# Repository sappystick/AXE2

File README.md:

# AXE2

AXE2 is a clean-sheet 1-inch (D233 × 25.4 mm) pulse-induction detector head. Every part is produced by a generator: the housing parts, the routed boards (KiCad + Gerbers), the system netlist, the checks and the physics studies. The whole set is driven by one smart runner. Split from [ARX](https://github.com/sappystick/ARX) on 2026-10-30.

**Status:** MODELED / tool-checked. See `STATUS.md` (generated) and `START_HERE.md`.

```bash
make tools            # install + self-test (KiCad 9, libraries, ngspice, gmsh, ARM gcc, Java 25 + Freerouting, pinned Python)
python3 run.py        # run only what is needed: failed / changed / missing / dependents
python3 run.py --failed
```

| Folder | Contents |
|---|---|
| `rf2/head/` | head generators: SPEC + housing (`rf2_head.py`), system netlist, boards (`rf2_boards.py`, display `rf2_ledgrid.py`, shield, receive-board variant), checks, renders; outputs in `rf2/head/out/` |
| `rf2/` | physics studies (coil formation, receivers, ground, EMI, timing, pinpoint, ...), results, handoff, parts, enhancement plan |
| `src/pcb/` | routing and board tools: Freerouting step (stall watchdog), A* fallback router, Gerber geometry, DRC helpers, SB1R generator |
| `reference/rf1/` | RF1 rigid-flex work: routed AB1A / AB1B, CB1D placement (Phase C starts here) |
| `data/` | datasheets (verified values in `docs/DATASHEET_LOG_ARX.md`), reference inputs |
| `state/` | runner ledger (results of every step); logs are not committed |
| `docs/` | references to ARX, corrections, assumptions, conventions |

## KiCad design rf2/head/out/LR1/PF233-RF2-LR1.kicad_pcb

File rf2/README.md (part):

# RF2 clean-sheet side experiment: transmit formation in a 1-inch head (MODELED)

Question (owner, 2026-10-29): inside the existing diameter and a 1-inch (25.4 mm) height, which layered / stacked / dense transmit-coil formation gives
the most depth together with the best signature data, with the dual-quadrupole receiver (RX-Q) and a central rigid-flex compute bay?
Nothing here touches the baseline. All numbers are MODELED: noise-limited, gold spheres, no ground, no bench data.

`rf2_coil_search.py` (about 20 s) -> `results/rf2_coil_search.json`; `rf2_figure.py` -> `results/rf2_coil_search.png`.

## Method
- Same physics as `src/sim/sim_head1.py`, re-parametrised: RX-Q geometry and noise, sphere step-off response, gate schedule, SNR 3, lateral search grid,
  the turn-off circuit and the first clean gate from the nulled turn-off tail (floor 6 us).
- **Fair comparison:** every candidate gets the baseline's energy per pulse at boost (1/2 x 54 uH x 20 A^2 = 10.8 mJ) and 20 A per switch. With the energy
  fixed, depth depends on the winding geometry through B / sqrt(L) only; the series / parallel split just trades current for inductance, and more switches
  (more total current at the same energy) make the turn-off faster.
- Coil: circular turns (exact elliptic-integral fields and inductances), litz 1.2 mm OD on a dense 1.6 mm grid, window z 3.2-21.9 mm (RX-Q boards below,
  lid + ferrite sheet + clearance above; the display sits in the centre bay), r up to 113.4 mm.
- **Validation:** the built coil through this chain: L 51.5 uH (model 54), 25.0 uT/A at 100 mm (24.56), moment 7.97 A m2 at 20 A (7.96), depth
  0.1 / 1 / 20 g = 90 / 134 / 188 mm (sim_head1: 91 / 136 / 189).

## Results (1 g / 0.1 g gold sphere, RX-Q)
| Formation | 1 g | 0.1 g | Notes |
|---|---|---|---|
| Built coil (25.6 mm tall, does not fit 1 in) | 134 | 90 | first gate 7.1 us |
| 1 in, dense window r 62-113 (spread) ... r 100-113 (rim), 1 switch | 136 | 91-92 | geometry changes depth by <= 1 mm at fixed energy |
| 1 in, rim r 100-113, 2 or 4 switches | 137 | 94 | turn-off 3.8 -> 1.9 us; first gate reaches the 6 us receiver floor |
| + ideal ferrite plane above (UPPER BOUND) | 143 | 98 | the real hood v3 model gave about half of an ideal plane's gain |
| Quadrant set, X mode (horizontal field, shape probe) | 131 | 93 | nearly as deep as the vertical mode with RX-Q |
| Built coil with the figure-8 receiver (sim_head1) | 152 | 99 | the receiver, not the transmit formation, is the largest depth lever |

First-gate sensitivity (4-switch rim coil): 6 / 4 / 3 / 2 us -> 0.05 g 79 / 85 / 88 / 91 mm, 0.1 g 94 / 98 / 100 / 102 mm, 1 g 137 / 139 / 139 / 140 mm.

## Reading
1. **A 1-inch head costs no depth.** At the same pulse energy the dense 1-inch windings match or beat the 25.6 mm stacked coil (136-137 vs 134 mm).
2. **No transmit formation is a big depth lever in this footprint.** Spreading or concentrating the turns, stacking or not: <= 2 mm. Depth moves with
   pulse energy (signal ~ sqrt(E): 2 x energy -> about +7 %), the receiver (figure-8 152 vs RX-Q 136 mm: RX-Q trades about 11 % depth for bearing and
   pinpoint), noise and averaging.
3. **Best formation for depth + signature:** a dense rim winding (r about 100-113 mm, full window height) split into interleaved full-ring branches on
   2-4 switches: fastest turn-off at the same energy (better small / fast targets once the receiver recovers sooner), same depth, frees the centre bay.
4. **Quadrant windings (Z + X / Y modes) give a strong shape channel (X mode 131 mm at 1 g) but a 1 % current mismatch between quadrants puts about
   0.49 V into RX-Q at turn-off** (the built coil's aligned leak is 0.01 mV). The vertical mode must stay on symmetric full-ring branches; X / Y needs
   its own matched pair winding and a receiver that recovers from that leak. Not yet modeled: the pairs' turn-off, X-mode energy, recovery.
5. **Small targets:** the remaining limit is the receiver recovery floor, not the coil: 6 -> 2 us adds about 15 % depth on 0.05 g.

## Not modeled
Ground (mineralisation: the early gates that help small gold also see more ground), coil self-capacitance, litz AC resistance, eddy currents in the head
and the compute bay, the real (finite) ferrite sheet, thermal. Next if pursued: figure-8 / DD / concentric receive options in the same chain with the
rim coil, a matched X / Y pair winding with its turn-off and leak, a finite ferrite sheet, and ground.

## Step 2: receiver architecture, light coil, mass, and an SDC 2300-class comparison (`rf2_receiver_combo.py`, `results/rf2_receiver_combo.{json,png}`)
Owner: targets of 1 g and up only. Same physics and equal energy per pulse (10.8 mJ); every receive channel read with the same preamp noise (1.7 nV/rtHz).

| Architecture (1-inch head, rim transmit coil) | 1 g | 5 g | 20 g | Uniform-ground coupling (rel. CN) |
|---|---|---|---|---|
| QUAD only (built receiver) | 137 | 165 | 190 | 0 by symmetry |
| Figure-8 only (check: sim_head1 at the same noise gives 179 mm at 1 g) | 181 | 223 | 262 | 0 by symmetry |
| Concentric nulled (12 turns r 80-95, 26 bucking turns r 65) | 231 | 284 | 337 | 1.0 |
| **Proposed: rim mono (26 turns, 321 uH, 8.2 A) + QUAD board, mono channel, 15 us gate** | **345** | **439** | **>= 500** | 1.44 |
| same, QUAD channel (bearing, pinpoint, depth ratio) | 131 | 162 | 189 | 0 by symmetry |
| SDC 2300-class 8 in mono at EQUAL electronics, 10 us gate (internals ASSUMED) | 330 | 413 | 494 | 1.40 |

- **Light transmit winding:** 24 turns (16.9 m of litz) give the same depth as the 99-turn dense window (66.6 m): at fixed energy only B / sqrt(L) counts.
- **Depth readout:** the QUAD / mono peak-signal ratio falls monotonically with depth (0.118 / 0.026 / 0.0094 / 0.0043 / 0.0019 at 50 / 100 / 150 / 200 / 300 mm),
  independent of target size for a sphere: depth from the ratio, then size from the amplitude at that depth, type from the decay time constant.
- **Head mass estimate: about 0.53 kg** (component estimates, not weighed; baseline head estimate 2.22 kg). The SDC 2300 is 2.3-2.4 kg as a whole
  detector without batteries; its coil mass is not published, so no head-to-head mass comparison is made.
- **SDC 2300 published facts used:** 8 in round mono, hardwired; Multi Period Fast PI; 2.3-2.4 kg without batteries; 4 x C cells, about 7 h; no
  discrimination, depth readout or pinpoint mode; LED indicator + audio; waterproof 3 m. Not published: turns, inductance, current, timing, noise, depth.
  The SDC row is therefore an 8 in mono with OUR electronics, not the real detector.
- **Reading:** the mono channel is the deepest receive option for >= 1 g (the full transmit coil is the receiver: the largest area); the proposed
  head's mono is about 4-5 % deeper than an 8 in mono at equal electronics, from the larger diameter only. What the proposed head adds is the QUAD
  channel (bearing, peak-null-peak pinpoint, a ground-symmetric second channel) and the ratio depth readout.
- **The bucking-turn cap:** an unconstrained concentric search chose 1239 turns at r 12 mm (cannot be laid out; capacitance and resistance noise not
  modeled); the search caps the bucking winding at 30 board-trace turns (0.3 mm pitch, 4 layers, a 6 mm band holds about 80).
- **Not modeled, and decisive in the field:** real ground. The mono and CN channels see a uniform viscous ground strongly and need ground balance
  (as the SDC has); the QUAD and figure-8 cancel uniform ground only while the head stays level and at constant height. Hot rocks, layering and
  sweep tilt are not modeled. Also not modeled: the mono's damping-resistor noise and preamp overload recovery (the 1.7 nV/rtHz is generous to both
  monos), self-capacitance, eddy currents in the compute bay.

## Step 3: mineralised ground and how to cancel it (`rf2_ground.py`, `results/rf2_ground.{json,png}`)
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
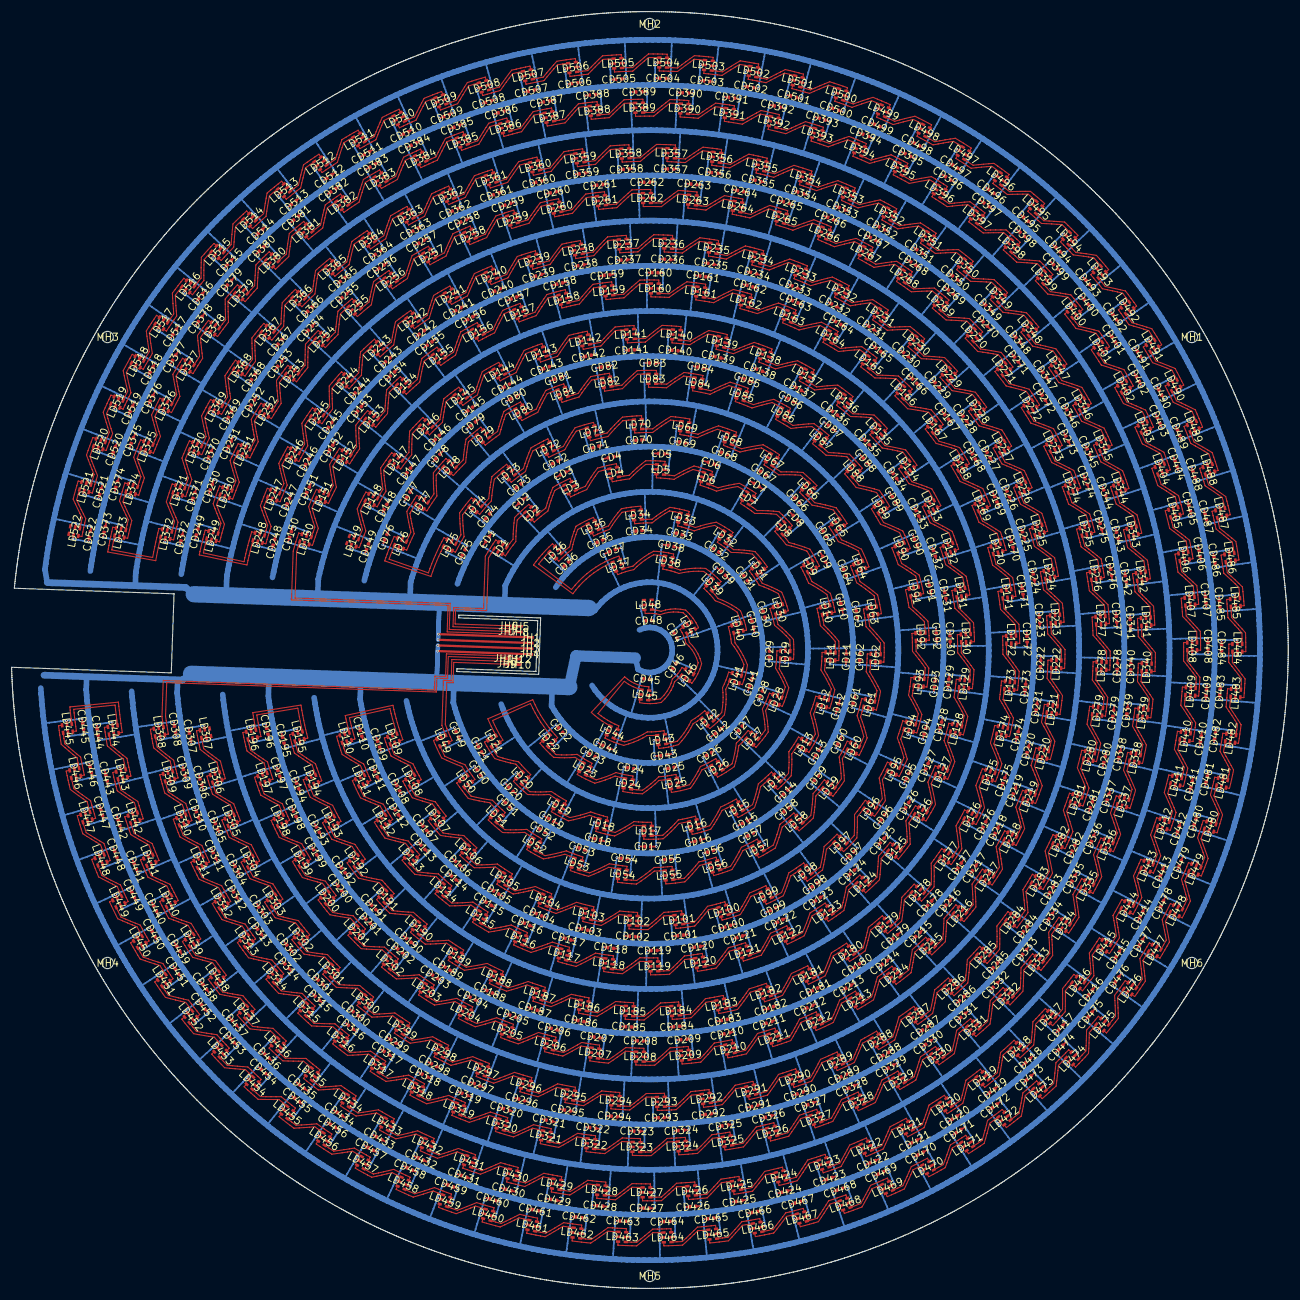
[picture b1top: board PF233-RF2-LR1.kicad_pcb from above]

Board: 2 copper layers, 226.0 x 226.0 mm, 1062 parts (0 on the bottom side), 1046 nets.

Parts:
CD1, CD2, CD3, CD4, CD5, CD6, CD7, CD8, CD9, CD10, CD11, CD12, CD13, CD14, CD15, CD16, CD17, CD18, CD19, CD20, CD21, CD22, CD23, CD24, CD25, CD26, CD27, CD28, CD29, CD30, CD31, CD32, CD33, CD34, CD35, CD36, CD37, CD38, CD39, CD40, CD41, CD42, CD43, CD44, CD45, CD46, CD47, CD48, CD49, CD50, CD51, CD52, CD53, CD54, CD55, CD56, CD57, CD58, CD59, CD60, CD61, CD62, CD63, CD64, CD65, CD66, CD67, CD68, CD69, CD70, CD71, CD72, CD73, CD74, CD75, CD76, CD77, CD78, CD79, CD80, CD81, CD82, CD83, CD84, CD85, CD86, CD87, CD88, CD89, CD90, CD91, CD92, CD93, CD94, CD95, CD96, CD97, CD98, CD99, CD100, CD101, CD102, CD103, CD104, CD105, CD106, CD107, CD108, CD109, CD110, CD111, CD112, CD113, CD114, CD115, CD116, CD117, CD118, CD119, CD120, CD121, CD122, CD123, CD124, CD125, CD126, CD127, CD128, CD129, CD130, CD131, CD132, CD133, CD134, CD135, CD136, CD137, CD138, CD139, CD140, CD141, CD142, CD143, CD144, CD145, CD146, CD147, CD148, CD149, CD150, CD151, CD152, CD153, CD154, CD155, CD156, CD157, CD158, CD159, CD160, CD161, CD162, CD163, CD164, CD165, CD166, CD167, CD168, CD169, CD170, CD171, CD172, CD173, CD174, CD175, CD176, CD177, CD178, CD179, CD180, CD181, CD182, CD183, CD184, CD185, CD186, CD187, CD188, CD189, CD190, CD191, CD192, CD193, CD194, CD195, CD196, CD197, CD198, CD199, CD200, CD201, CD202, CD203, CD204, CD205, CD206, CD207, CD208, CD209, CD210, CD211, CD212, CD213, CD214, CD215, CD216, CD217, CD218, CD219, CD220, CD221, CD222, CD223, CD224, CD225, CD226, CD227, CD228, CD229, CD230, CD231, CD232, CD233, CD234, CD235, CD236, CD237, CD238, CD239, CD240, CD241, CD242, CD243, CD244, CD245, CD246, CD247, CD248, CD249, CD250, CD251, CD252, CD253, CD254, CD255, CD256, CD257, CD258, CD259, CD260, CD261, CD262, CD263, CD264, CD265, CD266, CD267, CD268, CD269, CD270, CD271, CD272, CD273, CD274, CD275, CD276, CD277, CD278, CD279, CD280, CD281, CD282, CD283, CD284, CD285, CD286, CD287, CD288, CD289, CD290, CD291, CD292, CD293, CD294, CD295, CD296, CD297, CD298, CD299, CD300, CD301, CD302, CD303, CD304, CD305, CD306, CD307, CD308, CD309, CD310, CD311, CD312, CD313, CD314, CD315, CD316, CD317, CD318, CD319, CD320, CD321, CD322, CD323, CD324, CD325, CD326, CD327, CD328, CD329, CD330, CD331, CD332, CD333, CD334, CD335, CD336, CD337, CD338, CD339, CD340, CD341, CD342, CD343, CD344, CD345, CD346, CD347, CD348, CD349, CD350, CD351, CD352, CD353, CD354, CD355, CD356, CD357, CD358, CD359, CD360, CD361, CD362, CD363, CD364, CD365, CD366, CD367, CD368, CD369, CD370, CD371, CD372, CD373, CD374, CD375, CD376, CD377, CD378, CD379, CD380, CD381, CD382, CD383, CD384, CD385, CD386, CD387, CD388, CD389, CD390, CD391, CD392, CD393, CD394, CD395, CD396, CD397, CD398, CD399, CD400, CD401, CD402, CD403, CD404, CD405, CD406, CD407, CD408, CD409, CD410, CD411, CD412, CD413, CD414, CD415, CD416, CD417, CD418, CD419, CD420, CD421, CD422, CD423, CD424, CD425, CD426, CD427, CD428, CD429, CD430, CD431, CD432, CD433, CD434, CD435, CD436, CD437, CD438, CD439, CD440, CD441, CD442, CD443, CD444, CD445, CD446, CD447, CD448, CD449, CD450, CD451, CD452, CD453, CD454, CD455, CD456, CD457, CD458, CD459, CD460, CD461, CD462, CD463, CD464, CD465, CD466, CD467, CD468, CD469, CD470, CD471, CD472, CD473, CD474, CD475, CD476, CD477, CD478, CD479, CD480, CD481, CD482, CD483, CD484, CD485, CD486, CD487, CD488, CD489, CD490, CD491, CD492, CD493, CD494, CD495, CD496, CD497, CD498, CD499, CD500, CD501, CD502, CD503, CD504, CD505, CD506, CD507, CD508, CD509, CD510, CD511, CD512, CD513, CD514, CD515, CD516, CD517, CD518, CD519, CD520, CD521, CD522: 100n; C0402
JH1, JH2: GND; FLEX_LAND
JH3, JH4: +5V_LED; FLEX_LAND
JH5: C1_K0; FLEX_LAND
JH6: C1_D0; FLEX_LAND
JH7: C3_D0; FLEX_LAND
JH8: C3_K0; FLEX_LAND
JH9: C2_K0; FLEX_LAND
JH10: C2_D0; FLEX_LAND
JH11: C4_K0; FLEX_LAND
JH12: C4_D0; FLEX_LAND
LD1, LD2, LD3, LD4, LD5, LD6, LD7, LD8, LD9, LD10, LD11, LD12, LD13, LD14, LD15, LD16, LD17, LD18, LD19, LD20, LD21, LD22, LD23, LD24, LD25, LD26, LD27, LD28, LD29, LD30, LD31, LD32, LD33, LD34, LD35, LD36, LD37, LD38, LD39, LD40, LD41, LD42, LD43, LD44, LD45, LD46, LD47, LD48, LD49, LD50, LD51, LD52, LD53, LD54, LD55, LD56, LD57, LD58, LD59, LD60, LD61, LD62, LD63, LD64, LD65, LD66, LD67, LD68, LD69, LD70, LD71, LD72, LD73, LD74, LD75, LD76, LD77, LD78, LD79, LD80, LD81, LD82, LD83, LD84, LD85, LD86, LD87, LD88, LD89, LD90, LD91, LD92, LD93, LD94, LD95, LD96, LD97, LD98, LD99, LD100, LD101, LD102, LD103, LD104, LD105, LD106, LD107, LD108, LD109, LD110, LD111, LD112, LD113, LD114, LD115, LD116, LD117, LD118, LD119, LD120, LD121, LD122, LD123, LD124, LD125, LD126, LD127, LD128, LD129, LD130, LD131, LD132, LD133, LD134, LD135, LD136, LD137, LD138, LD139, LD140, LD141, LD142, LD143, LD144, LD145, LD146, LD147, LD148, LD149, LD150, LD151, LD152, LD153, LD154, LD155, LD156, LD157, LD158, LD159, LD160, LD161, LD162, LD163, LD164, LD165, LD166, LD167, LD168, LD169, LD170, LD171, LD172, LD173, LD174, LD175, LD176, LD177, LD178, LD179, LD180, LD181, LD182, LD183, LD184, LD185, LD186, LD187, LD188, LD189, LD190, LD191, LD192, LD193, LD194, LD195, LD196, LD197, LD198, LD199, LD200, LD201, LD202, LD203, LD204, LD205, LD206, LD207, LD208, LD209, LD210, LD211, LD212, LD213, LD214, LD215, LD216, LD217, LD218, LD219, LD220, LD221, LD222, LD223, LD224, LD225, LD226, LD227, LD228, LD229, LD230, LD231, LD232, LD233, LD234, LD235, LD236, LD237, LD238, LD239, LD240, LD241, LD242, LD243, LD244, LD245, LD246, LD247, LD248, LD249, LD250, LD251, LD252, LD253, LD254, LD255, LD256, LD257, LD258, LD259, LD260, LD261, LD262, LD263, LD264, LD265, LD266, LD267, LD268, LD269, LD270, LD271, LD272, LD273, LD274, LD275, LD276, LD277, LD278, LD279, LD280, LD281, LD282, LD283, LD284, LD285, LD286, LD287, LD288, LD289, LD290, LD291, LD292, LD293, LD294, LD295, LD296, LD297, LD298, LD299, LD300, LD301, LD302, LD303, LD304, LD305, LD306, LD307, LD308, LD309, LD310, LD311, LD312, LD313, LD314, LD315, LD316, LD317, LD318, LD319, LD320, LD321, LD322, LD323, LD324, LD325, LD326, LD327, LD328, LD329, LD330, LD331, LD332, LD333, LD334, LD335, LD336, LD337, LD338, LD339, LD340, LD341, LD342, LD343, LD344, LD345, LD346, LD347, LD348, LD349, LD350, LD351, LD352, LD353, LD354, LD355, LD356, LD357, LD358, LD359, LD360, LD361, LD362, LD363, LD364, LD365, LD366, LD367, LD368, LD369, LD370, LD371, LD372, LD373, LD374, LD375, LD376, LD377, LD378, LD379, LD380, LD381, LD382, LD383, LD384, LD385, LD386, LD387, LD388, LD389, LD390, LD391, LD392, LD393, LD394, LD395, LD396, LD397, LD398, LD399, LD400, LD401, LD402, LD403, LD404, LD405, LD406, LD407, LD408, LD409, LD410, LD411, LD412, LD413, LD414, LD415, LD416, LD417, LD418, LD419, LD420, LD421, LD422, LD423, LD424, LD425, LD426, LD427, LD428, LD429, LD430, LD431, LD432, LD433, LD434, LD435, LD436, LD437, LD438, LD439, LD440, LD441, LD442, LD443, LD444, LD445, LD446, LD447, LD448, LD449, LD450, LD451, LD452, LD453, LD454, LD455, LD456, LD457, LD458, LD459, LD460, LD461, LD462, LD463, LD464, LD465, LD466, LD467, LD468, LD469, LD470, LD471, LD472, LD473, LD474, LD475, LD476, LD477, LD478, LD479, LD480, LD481, LD482, LD483, LD484, LD485, LD486, LD487, LD488, LD489, LD490, LD491, LD492, LD493, LD494, LD495, LD496, LD497, LD498, LD499, LD500, LD501, LD502, LD503, LD504, LD505, LD506, LD507, LD508, LD509, LD510, LD511, LD512, LD513, LD514, LD515, LD516, LD517, LD518, LD519, LD520, LD521, LD522: SK9822-EC20; SK9822EC20
MH1, MH2, MH3, MH4, MH5, MH6: MountingHole_2.0mm

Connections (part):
+5V_LED: CD1.1, CD2.1, CD3.1, CD4.1, CD5.1, CD6.1, CD7.1, CD8.1, CD9.1, CD10.1, CD11.1, CD12.1, CD13.1, CD14.1, CD15.1, CD16.1, CD17.1, CD18.1, CD19.1, CD20.1, CD21.1, CD22.1, CD23.1, CD24.1, CD25.1, CD26.1, CD27.1, CD28.1, CD29.1, CD30.1, CD31.1, CD32.1, CD33.1, CD34.1, CD35.1, CD36.1, CD37.1, CD38.1, CD39.1, CD40.1, CD41.1, CD42.1, CD43.1, CD44.1, CD45.1, CD46.1, CD47.1, CD48.1, CD49.1, CD50.1, CD51.1, CD52.1, CD53.1, CD54.1, CD55.1, CD56.1, CD57.1, CD58.1, CD59.1, CD60.1, CD61.1, CD62.1, CD63.1, CD64.1, CD65.1, CD66.1, CD67.1, CD68.1, CD69.1, CD70.1, CD71.1, CD72.1, CD73.1, CD74.1, CD75.1, CD76.1, CD77.1, CD78.1, CD79.1, CD80.1, CD81.1, CD82.1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
C1_D0: JH6.1, LD1.3
C1_D1: LD1.1, LD2.3
C1_D2: LD2.1, LD3.3
C1_D3: LD3.1, LD4.3
C1_D4: LD4.1, LD5.3
C1_D5: LD5.1, LD6.3
C1_D6: LD6.1, LD7.3
C1_D7: LD7.1, LD8.3
C1_D8: LD8.1, LD9.3
C1_D9: LD9.1, LD10.3
C1_D10: LD10.1, LD11.3
C1_D11: LD11.1, LD12.3
C1_D12: LD12.1, LD13.3
C1_D13: LD13.1, LD14.3
C1_D14: LD14.1, LD15.3
C1_D15: LD15.1, LD16.3
C1_D16: LD16.1, LD17.3
C1_D17: LD17.1, LD18.3
C1_D18: LD18.1, LD19.3
C1_D19: LD19.1, LD20.3
C1_D20: LD20.1, LD21.3
C1_D21: LD21.1, LD22.3
C1_D22: LD22.1, LD23.3
C1_D23: LD23.1, LD24.3
C1_D24: LD24.1, LD25.3
C1_D25: LD25.1, LD26.3
C1_D26: LD26.1, LD27.3
C1_D27: LD27.1, LD28.3
C1_D28: LD28.1, LD29.3
C1_D29: LD29.1, LD30.3
C1_D30: LD30.1, LD31.3
C1_D31: LD31.1, LD32.3
C1_D32: LD32.1, LD33.3
C1_D33: LD33.1, LD34.3
C1_D34: LD34.1, LD35.3
C1_D35: LD35.1, LD36.3
C1_D36: LD36.1, LD37.3
C1_D37: LD37.1, LD38.3
C1_D38: LD38.1, LD39.3
C1_D39: LD39.1, LD40.3
C1_D40: LD40.1, LD41.3
C1_D41: LD41.1, LD42.3
C1_D42: LD42.1, LD43.3
C1_D43: LD43.1, LD44.3
C1_D44: LD44.1, LD45.3
C1_D45: LD45.1, LD46.3
C1_D46: LD46.1, LD47.3
C1_D47: LD47.1, LD48.3
C1_K0: JH5.1, LD1.4
C1_K1: LD1.6, LD2.4
C1_K2: LD2.6, LD3.4
C1_K3: LD3.6, LD4.4
C1_K4: LD4.6, LD5.4
C1_K5: LD5.6, LD6.4
C1_K6: LD6.6, LD7.4
C1_K7: LD7.6, LD8.4
C1_K8: LD8.6, LD9.4
C1_K9: LD9.6, LD10.4
C1_K10: LD10.6, LD11.4
C1_K11: LD11.6, LD12.4
C1_K12: LD12.6, LD13.4
C1_K13: LD13.6, LD14.4
C1_K14: LD14.6, LD15.4
C1_K15: LD15.6, LD16.4
C1_K16: LD16.6, LD17.4
C1_K17: LD17.6, LD18.4
C1_K18: LD18.6, LD19.4
C1_K19: LD19.6, LD20.4
C1_K20: LD20.6, LD21.4
C1_K21: LD21.6, LD22.4
C1_K22: LD22.6, LD23.4
C1_K23: LD23.6, LD24.4
C1_K24: LD24.6, LD25.4
C1_K25: LD25.6, LD26.4
C1_K26: LD26.6, LD27.4
C1_K27: LD27.6, LD28.4
C1_K28: LD28.6, LD29.4
C1_K29: LD29.6, LD30.4
C1_K30: LD30.6, LD31.4
C1_K31: LD31.6, LD32.4
C1_K32: LD32.6, LD33.4
C1_K33: LD33.6, LD34.4
C1_K34: LD34.6, LD35.4
C1_K35: LD35.6, LD36.4
C1_K36: LD36.6, LD37.4
C1_K37: LD37.6, LD38.4
C1_K38: LD38.6, LD39.4
C1_K39: LD39.6, LD40.4
C1_K40: LD40.6, LD41.4
C1_K41: LD41.6, LD42.4
C1_K42: LD42.6, LD43.4
C1_K43: LD43.6, LD44.4
C1_K44: LD44.6, LD45.4
C1_K45: LD45.6, LD46.4
C1_K46: LD46.6, LD47.4
C1_K47: LD47.6, LD48.4
C2_D0: JH10.1, LD49.3
C2_D1: LD49.1, LD50.3
C2_D2: LD50.1, LD51.3
C2_D3: LD51.1, LD52.3
C2_D4: LD52.1, LD53.3
C2_D5: LD53.1, LD54.3
C2_D6: LD54.1, LD55.3
C2_D7: LD55.1, LD56.3
C2_D8: LD56.1, LD57.3
C2_D9: LD57.1, LD58.3
C2_D10: LD58.1, LD59.3
C2_D11: LD59.1, LD60.3
C2_D12: LD60.1, LD61.3
C2_D13: LD61.1, LD62.3
C2_D14: LD62.1, LD63.3
C2_D15: LD63.1, LD64.3
C2_D16: LD64.1, LD65.3
C2_D17: LD65.1, LD66.3
C2_D18: LD66.1, LD67.3
C2_D19: LD67.1, LD68.3
C2_D20: LD68.1, LD69.3
C2_D21: LD69.1, LD70.3
C2_D22: LD70.1, LD71.3
C2_D23: LD71.1, LD72.3
C2_D24: LD72.1, LD73.3
C2_D25: LD73.1, LD74.3
C2_D26: LD74.1, LD75.3
C2_D27: LD75.1, LD76.3
C2_D28: LD76.1, LD77.3
C2_D29: LD77.1, LD78.3
C2_D30: LD78.1, LD79.3
C2_D31: LD79.1, LD80.3
C2_D32: LD80.1, LD81.3
C2_D33: LD81.1, LD82.3
C2_D34: LD82.1, LD83.3
C2_D35: LD83.1, LD84.3
C2_D36: LD84.1, LD85.3
C2_D37: LD85.1, LD86.3
C2_D38: LD86.1, LD87.3
C2_D39: LD87.1, LD88.3
C2_D40: LD88.1, LD89.3
C2_D41: LD89.1, LD90.3
C2_D42: LD90.1, LD91.3
C2_D43: LD91.1, LD92.3
C2_D44: LD92.1, LD93.3
C2_D45: LD93.1, LD94.3
C2_D46: LD94.1, LD95.3
C2_D47: LD95.1, LD96.3
C2_D48: LD96.1, LD97.3
C2_D49: LD97.1, LD98.3
C2_D50: LD98.1, LD99.3
C2_D51: LD99.1, LD100.3
C2_D52: LD100.1, LD101.3
C2_D53: LD101.1, LD102.3
C2_D54: LD102.1, LD103.3
C2_D55: LD103.1, LD104.3
C2_D56: LD104.1, LD105.3
C2_D57: LD105.1, LD106.3
C2_D58: LD106.1, LD107.3
C2_D59: LD107.1, LD108.3
C2_D60: LD108.1, LD109.3
C2_D61: LD109.1, LD110.3
C2_D62: LD110.1, LD111.3
C2_D63: LD111.1, LD112.3
C2_D64: LD112.1, LD113.3
C2_D65: LD113.1, LD114.3
C2_D66: LD114.1, LD115.3
C2_D67: LD115.1, LD116.3
C2_D68: LD116.1, LD117.3
C2_D69: LD117.1, LD118.3
C2_D70: LD118.1, LD119.3
C2_D71: LD119.1, LD120.3
C2_D72: LD120.1, LD121.3
C2_D73: LD121.1, LD122.3
C2_D74: LD122.1, LD123.3
C2_D75: LD123.1, LD124.3
C2_D76: LD124.1, LD125.3
C2_D77: LD125.1, LD126.3
C2_D78: LD126.1, LD127.3
C2_D79: LD127.1, LD128.3
C2_D80: LD128.1, LD129.3
C2_D81: LD129.1, LD130.3
C2_D82: LD130.1, LD131.3
C2_D83: LD131.1, LD132.3
C2_D84: LD132.1, LD133.3
C2_D85: LD133.1, LD134.3
C2_D86: LD134.1, LD135.3
C2_D87: LD135.1, LD136.3
C2_D88: LD136.1, LD137.3
C2_D89: LD137.1, LD138.3
C2_D90: LD138.1, LD139.3
C2_D91: LD139.1, LD140.3
C2_D92: LD140.1, LD141.3
C2_D93: LD141.1, LD142.3
C2_D94: LD142.1, LD143.3
C2_D95: LD143.1, LD144.3
C2_D96: LD144.1, LD145.3
C2_D97: LD145.1, LD146.3
C2_D98: LD146.1, LD147.3
C2_D99: LD147.1, LD148.3
C2_D100: LD148.1, LD149.3
C2_K0: JH9.1, LD49.4
C2_K1: LD49.6, LD50.4
C2_K2: LD50.6, LD51.4
C2_K3: LD51.6, LD52.4
C2_K4: LD52.6, LD53.4
C2_K5: LD53.6, LD54.4
C2_K6: LD54.6, LD55.4
C2_K7: LD55.6, LD56.4
C2_K8: LD56.6, LD57.4
C2_K9: LD57.6, LD58.4
C2_K10: LD58.6, LD59.4
C2_K11: LD59.6, LD60.4
C2_K12: LD60.6, LD61.4
C2_K13: LD61.6, LD62.4
C2_K14: LD62.6, LD63.4
C2_K15: LD63.6, LD64.4
C2_K16: LD64.6, LD65.4
C2_K17: LD65.6, LD66.4
C2_K18: LD66.6, LD67.4
C2_K19: LD67.6, LD68.4
C2_K20: LD68.6, LD69.4
C2_K21: LD69.6, LD70.4
C2_K22: LD70.6, LD71.4
C2_K23: LD71.6, LD72.4
C2_K24: LD72.6, LD73.4
C2_K25: LD73.6, LD74.4
C2_K26: LD74.6, LD75.4
C2_K27: LD75.6, LD76.4
C2_K28: LD76.6, LD77.4
C2_K29: LD77.6, LD78.4
C2_K30: LD78.6, LD79.4
C2_K31: LD79.6, LD80.4
C2_K32: LD80.6, LD81.4
C2_K33: LD81.6, LD82.4
C2_K34: LD82.6, LD83.4
C2_K35: LD83.6, LD84.4
C2_K36: LD84.6, LD85.4
C2_K37: LD85.6, LD86.4
C2_K38: LD86.6, LD87.4
C2_K39: LD87.6, LD88.4
C2_K40: LD88.6, LD89.4
C2_K41: LD89.6, LD90.4
C2_K42: LD90.6, LD91.4
C2_K43: LD91.6, LD92.4
C2_K44: LD92.6, LD93.4
C2_K45: LD93.6, LD94.4
C2_K46: LD94.6, LD95.4
C2_K47: LD95.6, LD96.4
C2_K48: LD96.6, LD97.4
C2_K49: LD97.6, LD98.4
C2_K50: LD98.6, LD99.4
C2_K51: LD99.6, LD100.4
C2_K52: LD100.6, LD101.4
C2_K53: LD101.6, LD102.4
C2_K54: LD102.6, LD103.4
C2_K55: LD103.6, LD104.4
C2_K56: LD104.6, LD105.4
C2_K57: LD105.6, LD106.4
C2_K58: LD106.6, LD107.4
C2_K59: LD107.6, LD108.4
C2_K60: LD108.6, LD109.4
C2_K61: LD109.6, LD110.4
C2_K62: LD110.6, LD111.4
C2_K63: LD111.6, LD112.4
C2_K64: LD112.6, LD113.4
C2_K65: LD113.6, LD114.4
C2_K66: LD114.6, LD115.4
C2_K67: LD115.6, LD116.4
C2_K68: LD116.6, LD117.4
C2_K69: LD117.6, LD118.4
C2_K70: LD118.6, LD119.4
C2_K71: LD119.6, LD120.4
C2_K72: LD120.6, LD121.4
C2_K73: LD121.6, LD122.4
C2_K74: LD122.6, LD123.4
C2_K75: LD123.6, LD124.4
C2_K76: LD124.6, LD125.4
C2_K77: LD125.6, LD126.4
C2_K78: LD126.6, LD127.4
C2_K79: LD127.6, LD128.4
C2_K80: LD128.6, LD129.4
C2_K81: LD129.6, LD130.4
C2_K82: LD130.6, LD131.4
C2_K83: LD131.6, LD132.4
C2_K84: LD132.6, LD133.4
C2_K85: LD133.6, LD134.4
C2_K86: LD134.6, LD135.4
C2_K87: LD135.6, LD136.4
C2_K88: LD136.6, LD137.4
C2_K89: LD137.6, LD138.4
C2_K90: LD138.6, LD139.4
C2_K91: LD139.6, LD140.4
C2_K92: LD140.6, LD141.4
C2_K93: LD141.6, LD142.4
C2_K94: LD142.6, LD143.4
C2_K95: LD143.6, LD144.4
C2_K96: LD144.6, LD145.4
C2_K97: LD145.6, LD146.4
C2_K98: LD146.6, LD147.4
C2_K99: LD147.6, LD148.4
C2_K100: LD148.6, LD149.4
C3_D0: JH7.1, LD150.3
C3_D1: LD150.1, LD151.3
C3_D2: LD151.1, LD152.3
C3_D3: LD152.1, LD153.3
C3_D4: LD153.1, LD154.3
C3_D5: LD154.1, LD155.3
C3_D6: LD155.1, LD156.3
C3_D7: LD156.1, LD157.3
C3_D8: LD157.1, LD158.3
C3_D9: LD158.1, LD159.3
C3_D10: LD159.1, LD160.3
C3_D11: LD160.1, LD161.3
C3_D12: LD161.1, LD162.3
C3_D13: LD162.1, LD163.3
C3_D14: LD163.1, LD164.3
C3_D15: LD164.1, LD165.3
C3_D16: LD165.1, LD166.3
C3_D17: LD166.1, LD167.3
C3_D18: LD167.1, LD168.3
C3_D19: LD168.1, LD169.3
C3_D20: LD169.1, LD170.3
C3_D21: LD170.1, LD171.3
C3_D22: LD171.1, LD172.3
C3_D23: LD172.1, LD173.3
C3_D24: LD173.1, LD174.3
C3_D25: LD174.1, LD175.3
C3_D26: LD175.1, LD176.3
C3_D27: LD176.1, LD177.3
C3_D28: LD177.1, LD178.3
C3_D29: LD178.1, LD179.3
C3_D30: LD179.1, LD180.3
C3_D31: LD180.1, LD181.3
C3_D32: LD181.1, LD182.3
C3_D33: LD182.1, LD183.3
C3_D34: LD183.1, LD184.3
C3_D35: LD184.1, LD185.3
C3_D36: LD185.1, LD186.3
C3_D37: LD186.1, LD187.3
C3_D38: LD187.1, LD188.3
C3_D39: LD188.1, LD189.3
C3_D40: LD189.1, LD190.3
C3_D41: LD190.1, LD191.3
C3_D42: LD191.1, LD192.3
C3_D43: LD192.1, LD193.3
C3_D44: LD193.1, LD194.3
C3_D45: LD194.1, LD195.3
C3_D46: LD195.1, LD196.3
C3_D47: LD196.1, LD197.3
C3_D48: LD197.1, LD198.3
C3_D49: LD198.1, LD199.3
C3_D50: LD199.1, LD200.3
C3_D51: LD200.1, LD201.3
C3_D52: LD201.1, LD202.3
C3_D53: LD202.1, LD203.3
C3_D54: LD203.1, LD204.3
C3_D55: LD204.1, LD205.3
C3_D56: LD205.1, LD206.3
C3_D57: LD206.1, LD207.3
C3_D58: LD207.1, LD208.3
C3_D59: LD208.1, LD209.3
C3_D60: LD209.1, LD210.3
C3_D61: LD210.1, LD211.3
C3_D62: LD211.1, LD212.3
C3_D63: LD212.1, LD213.3
C3_D64: LD213.1, LD214.3
C3_D65: LD214.1, LD215.3
C3_D66: LD215.1, LD216.3
C3_D67: LD216.1, LD217.3
C3_D68: LD217.1, LD218.3
C3_D69: LD218.1, LD219.3
C3_D70: LD219.1, LD220.3
C3_D71: LD220.1, LD221.3
C3_D72: LD221.1, LD222.3
C3_D73: LD222.1, LD223.3
C3_D74: LD223.1, LD224.3
C3_D75: LD224.1, LD225.3
C3_D76: LD225.1, LD226.3
C3_D77: LD226.1, LD227.3
C3_D78: LD227.1, LD228.3
C3_D79: LD228.1, LD229.3
C3_D80: LD229.1, LD230.3
C3_D81: LD230.1, LD231.3
C3_D82: LD231.1, LD232.3
C3_D83: LD232.1, LD233.3
C3_D84: LD233.1, LD234.3
C3_D85: LD234.1, LD235.3
C3_D86: LD235.1, LD236.3
C3_D87: LD236.1, LD237.3
C3_D88: LD237.1, LD238.3
C3_D89: LD238.1, LD239.3
C3_D90: LD239.1, LD240.3
C3_D91: LD240.1, LD241.3
C3_D92: LD241.1, LD242.3
C3_D93: LD242.1, LD243.3
C3_D94: LD243.1, LD244.3
C3_D95: LD244.1, LD245.3
C3_D96: LD245.1, LD246.3
C3_D97: LD246.1, LD247.3
C3_D98: LD247.1, LD248.3
C3_D99: LD248.1, LD249.3
C3_D100: LD249.1, LD250.3
C3_D101: LD250.1, LD251.3
C3_D102: LD251.1, LD252.3
C3_D103: LD252.1, LD253.3
C3_D104: LD253.1, LD254.3
C3_D105: LD254.1, LD255.3
C3_D106: LD255.1, LD256.3
C3_D107: LD256.1, LD257.3
C3_D108: LD257.1, LD258.3
C3_D109: LD258.1, LD259.3
C3_D110: LD259.1, LD260.3
C3_D111: LD260.1, LD261.3
C3_D112: LD261.1, LD262.3
C3_D113: LD262.1, LD263.3
C3_D114: LD263.1, LD264.3
C3_D115: LD264.1, LD265.3
C3_D116: LD265.1, LD266.3
C3_D117: LD266.1, LD267.3
C3_D118: LD267.1, LD268.3
C3_D119: LD268.1, LD269.3
C3_D120: LD269.1, LD270.3
C3_D121: LD270.1, LD271.3
C3_D122: LD271.1, LD272.3
C3_D123: LD272.1, LD273.3
C3_D124: LD273.1, LD274.3
C3_D125: LD274.1, LD275.3
C3_D126: LD275.1, LD276.3
C3_D127: LD276.1, LD277.3
C3_D128: LD277.1, LD278.3
C3_D129: LD278.1, LD279.3
C3_D130: LD279.1, LD280.3
C3_D131: LD280.1, LD281.3
C3_D132: LD281.1, LD282.3
C3_D133: LD282.1, LD283.3
C3_D134: LD283.1, LD284.3
C3_D135: LD284.1, LD285.3
C3_D136: LD285.1, LD286.3
C3_D137: LD286.1, LD287.3
C3_D138: LD287.1, LD288.3
C3_D139: LD288.1, LD289.3
C3_D140: LD289.1, LD290.3
C3_D141: LD290.1, LD291.3
C3_D142: LD291.1, LD292.3
C3_D143: LD292.1, LD293.3
C3_D144: LD293.1, LD294.3
C3_D145: LD294.1, LD295.3
C3_D146: LD295.1, LD296.3
C3_D147: LD296.1, LD297.3
C3_D148: LD297.1, LD298.3
C3_D149: LD298.1, LD299.3
C3_D150: LD299.1, LD300.3
C3_D151: LD300.1, LD301.3
C3_D152: LD301.1, LD302.3
C3_D153: LD302.1, LD303.3
C3_D154: LD303.1, LD304.3
C3_D155: LD304.1, LD305.3
C3_D156: LD305.1, LD306.3
C3_D157: LD306.1, LD307.3
C3_K0: JH8.1, LD150.4
C3_K1: LD150.6, LD151.4
C3_K2: LD151.6, LD152.4
C3_K3: LD152.6, LD153.4
C3_K4: LD153.6, LD154.4
C3_K5: LD154.6, LD155.4
C3_K6: LD155.6, LD156.4
C3_K7: LD156.6, LD157.4
C3_K8: LD157.6, LD158.4
C3_K9: LD158.6, LD159.4
C3_K10: LD159.6, LD160.4
C3_K11: LD160.6, LD161.4
C3_K12: LD161.6, LD162.4
C3_K13: LD162.6, LD163.4
C3_K14: LD163.6, LD164.4
C3_K15: LD164.6, LD165.4
C3_K16: LD165.6, LD166.4
C3_K17: LD166.6, LD167.4
C3_K18: LD167.6, LD168.4
C3_K19: LD168.6, LD169.4
C3_K20: LD169.6, LD170.4
C3_K21: LD170.6, LD171.4
C3_K22: LD171.6, LD172.4
C3_K23: LD172.6, LD173.4
C3_K24: LD173.6, LD174.4
C3_K25: LD174.6, LD175.4
C3_K26: LD175.6, LD176.4
C3_K27: LD176.6, LD177.4
C3_K28: LD177.6, LD178.4
C3_K29: LD178.6, LD179.4
C3_K30: LD179.6, LD180.4
C3_K31: LD180.6, LD181.4
C3_K32: LD181.6, LD182.4
C3_K33: LD182.6, LD183.4
C3_K34: LD183.6, LD184.4
C3_K35: LD184.6, LD185.4
C3_K36: LD185.6, LD186.4
C3_K37: LD186.6, LD187.4
C3_K38: LD187.6, LD188.4
C3_K39: LD188.6, LD189.4
C3_K40: LD189.6, LD190.4
C3_K41: LD190.6, LD191.4
C3_K42: LD191.6, LD192.4
C3_K43: LD192.6, LD193.4
C3_K44: LD193.6, LD194.4
C3_K45: LD194.6, LD195.4
C3_K46: LD195.6, LD196.4
C3_K47: LD196.6, LD197.4
C3_K48: LD197.6, LD198.4
C3_K49: LD198.6, LD199.4
C3_K50: LD199.6, LD200.4
C3_K51: LD200.6, LD201.4
C3_K52: LD201.6, LD202.4
C3_K53: LD202.6, LD203.4
C3_K54: LD203.6, LD204.4
C3_K55: LD204.6, LD205.4
C3_K56: LD205.6, LD206.4
C3_K57: LD206.6, LD207.4
C3_K58: LD207.6, LD208.4
C3_K59: LD208.6, LD209.4
C3_K60: LD209.6, LD210.4
C3_K61: LD210.6, LD211.4
C3_K62: LD211.6, LD212.4
C3_K63: LD212.6, LD213.4
C3_K64: LD213.6, LD214.4
C3_K65: LD214.6, LD215.4
C3_K66: LD215.6, LD216.4
C3_K67: LD216.6, LD217.4
C3_K68: LD217.6, LD218.4
C3_K69: LD218.6, LD219.4
C3_K70: LD219.6, LD220.4
C3_K71: LD220.6, LD221.4
C3_K72: LD221.6, LD222.4
C3_K73: LD222.6, LD223.4
C3_K74: LD223.6, LD224.4
C3_K75: LD224.6, LD225.4
C3_K76: LD225.6, LD226.4
C3_K77: LD226.6, LD227.4
C3_K78: LD227.6, LD228.4
C3_K79: LD228.6, LD229.4
C3_K80: LD229.6, LD230.4
C3_K81: LD230.6, LD231.4
C3_K82: LD231.6, LD232.4
C3_K83: LD232.6, LD233.4
C3_K84: LD233.6, LD234.4
C3_K85: LD234.6, LD235.4
C3_K86: LD235.6, LD236.4
C3_K87: LD236.6, LD237.4
C3_K88: LD237.6, LD238.4
C3_K89: LD238.6, LD239.4
C3_K90: LD239.6, LD240.4
C3_K91: LD240.6, LD241.4
C3_K92: LD241.6, LD242.4
C3_K93: LD242.6, LD243.4
C3_K94: LD243.6, LD244.4
C3_K95: LD244.6, LD245.4
C3_K96: LD245.6, LD246.4
C3_K97: LD246.6, LD247.4
C3_K98: LD247.6, LD248.4
C3_K99: LD248.6, LD249.4
C3_K100: LD249.6, LD250.4
C3_K101: LD250.6, LD251.4
C3_K102: LD251.6, LD252.4
C3_K103: LD252.6, LD253.4
C3_K104: LD253.6, LD254.4
C3_K105: LD254.6, LD255.4
C3_K106: LD255.6, LD256.4
C3_K107: LD256.6, LD257.4
C3_K108: LD257.6, LD258.4
C3_K109: LD258.6, LD259.4
C3_K110: LD259.6, LD260.4
C3_K111: LD260.6, LD261.4
C3_K112: LD261.6, LD262.4
C3_K113: LD262.6, LD263.4
C3_K114: LD263.6, LD264.4
C3_K115: LD264.6, LD265.4
C3_K116: LD265.6, LD266.4
C3_K117: LD266.6, LD267.4
C3_K118: LD267.6, LD268.4
C3_K119: LD268.6, LD269.4
C3_K120: LD269.6, LD270.4
C3_K121: LD270.6, LD271.4
C3_K122: LD271.6, LD272.4
C3_K123: LD272.6, LD273.4
C3_K124: LD273.6, LD274.4
C3_K125: LD274.6, LD275.4
C3_K126: LD275.6, LD276.4
C3_K127: LD276.6, LD277.4
C3_K128: LD277.6, LD278.4
C3_K129: LD278.6, LD279.4
C3_K130: LD279.6, LD280.4
C3_K131: LD280.6, LD281.4
C3_K132: LD281.6, LD282.4
C3_K133: LD282.6, LD283.4
C3_K134: LD283.6, LD284.4
C3_K135: LD284.6, LD285.4
C3_K136: LD285.6, LD286.4
C3_K137: LD286.6, LD287.4
C3_K138: LD287.6, LD288.4
C3_K139: LD288.6, LD289.4
C3_K140: LD289.6, LD290.4
C3_K141: LD290.6, LD291.4
C3_K142: LD291.6, LD292.4
C3_K143: LD292.6, LD293.4
C3_K144: LD293.6, LD294.4
C3_K145: LD294.6, LD295.4
C3_K146: LD295.6, LD296.4
C3_K147: LD296.6, LD297.4
C3_K148: LD297.6, LD298.4
C3_K149: LD298.6, LD299.4
C3_K150: LD299.6, LD300.4
C3_K151: LD300.6, LD301.4
C3_K152: LD301.6, LD302.4
C3_K153: LD302.6, LD303.4
C3_K154: LD303.6, LD304.4
C3_K155: LD304.6, LD305.4
C3_K156: LD305.6, LD306.4
C3_K157: LD306.6, LD307.4
C4_D0: JH12.1, LD308.3
C4_D1: LD308.1, LD309.3
C4_D2: LD309.1, LD310.3
C4_D3: LD310.1, LD311.3
C4_D4: LD311.1, LD312.3
C4_D5: LD312.1, LD313.3
C4_D6: LD313.1, LD314.3
C4_D7: LD314.1, LD315.3
C4_D8: LD315.1, LD316.3
C4_D9: LD316.1, LD317.3
C4_D10: LD317.1, LD318.3
C4_D11: LD318.1, LD319.3
C4_D12: LD319.1, LD320.3
C4_D13: LD320.1, LD321.3
C4_D14: LD321.1, LD322.3
C4_D15: LD322.1, LD323.3
C4_D16: LD323.1, LD324.3
C4_D17: LD324.1, LD325.3
C4_D18: LD325.1, LD326.3
C4_D19: LD326.1, LD327.3
C4_D20: LD327.1, LD328.3
C4_D21: LD328.1, LD329.3
C4_D22: LD329.1, LD330.3
C4_D23: LD330.1, LD331.3
C4_D24: LD331.1, LD332.3
C4_D25: LD332.1, LD333.3
C4_D26: LD333.1, LD334.3
C4_D27: LD334.1, LD335.3
C4_D28: LD335.1, LD336.3
C4_D29: LD336.1, LD337.3
C4_D30: LD337.1, LD338.3
C4_D31: LD338.1, LD339.3
C4_D32: LD339.1, LD340.3
C4_D33: LD340.1, LD341.3
C4_D34: LD341.1, LD342.3
C4_D35: LD342.1, LD343.3
C4_D36: LD343.1, LD344.3
C4_D37: LD344.1, LD345.3
C4_D38: LD345.1, LD346.3
C4_D39: LD346.1, LD347.3
C4_D40: LD347.1, LD348.3
C4_D41: LD348.1, LD349.3
C4_D42: LD349.1, LD350.3
C4_D43: LD350.1, LD351.3
C4_D44: LD351.1, LD352.3
C4_D45: LD352.1, LD353.3
C4_D46: LD353.1, LD354.3
C4_D47: LD354.1, LD355.3
C4_D48: LD355.1, LD356.3
C4_D49: LD356.1, LD357.3
C4_D50: LD357.1, LD358.3
C4_D51: LD358.1, LD359.3
C4_D52: LD359.1, LD360.3
C4_D53: LD360.1, LD361.3
C4_D54: LD361.1, LD362.3
C4_D55: LD362.1, LD363.3
C4_D56: LD363.1, LD364.3
C4_D57: LD364.1, LD365.3
C4_D58: LD365.1, LD366.3
C4_D59: LD366.1, LD367.3
C4_D60: LD367.1, LD368.3
C4_D61: LD368.1, LD369.3
C4_D62: LD369.1, LD370.3
C4_D63: LD370.1, LD371.3
C4_D64: LD371.1, LD372.3
C4_D65: LD372.1, LD373.3
C4_D66: LD373.1, LD374.3
C4_D67: LD374.1, LD375.3
C4_D68: LD375.1, LD376.3
C4_D69: LD376.1, LD377.3
C4_D70: LD377.1, LD378.3
C4_D71: LD378.1, LD379.3
C4_D72: LD379.1, LD380.3
C4_D73: LD380.1, LD381.3
C4_D74: LD381.1, LD382.3
C4_D75: LD382.1, LD383.3
C4_D76: LD383.1, LD384.3
C4_D77: LD384.1, LD385.3
C4_D78: LD385.1, LD386.3
C4_D79: LD386.1, LD387.3
C4_D80: LD387.1, LD388.3
C4_D81: LD388.1, LD389.3
C4_D82: LD389.1, LD390.3
C4_D83: LD390.1, LD391.3
C4_D84: LD391.1, LD392.3
C4_D85: LD392.1, LD393.3
C4_D86: LD393.1, LD394.3
C4_D87: LD394.1, LD395.3
C4_D88: LD395.1, LD396.3
C4_D89: LD396.1, LD397.3
C4_D90: LD397.1, LD398.3
C4_D91: LD398.1, LD399.3
C4_D92: LD399.1, LD400.3
C4_D93: LD400.1, LD401.3
C4_D94: LD401.1, LD402.3
C4_D95: LD402.1, LD403.3
C4_D96: LD403.1, LD404.3
C4_D97: LD404.1, LD405.3
C4_D98: LD405.1, LD406.3
C4_D99: LD406.1, LD407.3
C4_D100: LD407.1, LD408.3
C4_D101: LD408.1, LD409.3
C4_D102: LD409.1, LD410.3
C4_D103: LD410.1, LD411.3
C4_D104: LD411.1, LD412.3
C4_D105: LD412.1, LD413.3
C4_D106: LD413.1, LD414.3
C4_D107: LD414.1, LD415.3
C4_D108: LD415.1, LD416.3
C4_D109: LD416.1, LD417.3
C4_D110: LD417.1, LD418.3
C4_D111: LD418.1, LD419.3
C4_D112: LD419.1, LD420.3
C4_D113: LD420.1, LD421.3
C4_D114: LD421.1, LD422.3
C4_D115: LD422.1, LD423.3
C4_D116: LD423.1, LD424.3
C4_D117: LD424.1, LD425.3
C4_D118: LD425.1, LD426.3
C4_D119: LD426.1, LD427.3
C4_D120: LD427.1, LD428.3
C4_D121: LD428.1, LD429.3
C4_D122: LD429.1, LD430.3
C4_D123: LD430.1, LD431.3
C4_D124: LD431.1, LD432.3
C4_D125: LD432.1, LD433.3
C4_D126: LD433.1, LD434.3
C4_D127: LD434.1, LD435.3
C4_D128: LD435.1, LD436.3
C4_D129: LD436.1, LD437.3
C4_D130: LD437.1, LD438.3
C4_D131: LD438.1, LD439.3
C4_D132: LD439.1, LD440.3
C4_D133: LD440.1, LD441.3
C4_D134: LD441.1, LD442.3
C4_D135: LD442.1, LD443.3
C4_D136: LD443.1, LD444.3
C4_D137: LD444.1, LD445.3
C4_D138: LD445.1, LD446.3
C4_D139: LD446.1, LD447.3
C4_D140: LD447.1, LD448.3
C4_D141: LD448.1, LD449.3
C4_D142: LD449.1, LD450.3
C4_D143: LD450.1, LD451.3
C4_D144: LD451.1, LD452.3
C4_D145: LD452.1, LD453.3
C4_D146: LD453.1, LD454.3
C4_D147: LD454.1, LD455.3
C4_D148: LD455.1, LD456.3
C4_D149: LD456.1, LD457.3
C4_D150: LD457.1, LD458.3
C4_D151: LD458.1, LD459.3
C4_D152: LD459.1, LD460.3
C4_D153: LD460.1, LD461.3
C4_D154: LD461.1, LD462.3
C4_D155: LD462.1, LD463.3
C4_D156: LD463.1, LD464.3
C4_D157: LD464.1, LD465.3
C4_D158: LD465.1, LD466.3
C4_D159: LD466.1, LD467.3
C4_D160: LD467.1, LD468.3
C4_D161: LD468.1, LD469.3
C4_D162: LD469.1, LD470.3
C4_D163: LD470.1, LD471.3
C4_D164: LD471.1, LD472.3
C4_D165: LD472.1, LD473.3
C4_D166: LD473.1, LD474.3
C4_D167: LD474.1, LD475.3
C4_D168: LD475.1, LD476.3
C4_D169: LD476.1, LD477.3
C4_D170: LD477.1, LD478.3
C4_D171: LD478.1, LD479.3
C4_D172: LD479.1, LD480.3
C4_D173: LD480.1, LD481.3
C4_D174: LD481.1, LD482.3
C4_D175: LD482.1, LD483.3
C4_D176: LD483.1, LD484.3
C4_D177: LD484.1, LD485.3
C4_D178: LD485.1, LD486.3
C4_D179: LD486.1, LD487.3
C4_D180: LD487.1, LD488.3
C4_D181: LD488.1, LD489.3
C4_D182: LD489.1, LD490.3
C4_D183: LD490.1, LD491.3
C4_D184: LD491.1, LD492.3
C4_D185: LD492.1, LD493.3
C4_D186: LD493.1, LD494.3
C4_D187: LD494.1, LD495.3
C4_D188: LD495.1, LD496.3
C4_D189: LD496.1, LD497.3
C4_D190: LD497.1, LD498.3
C4_D191: LD498.1, LD499.3
C4_D192: LD499.1, LD500.3
C4_D193: LD500.1, LD501.3
C4_D194: LD501.1, LD502.3
C4_D195: LD502.1, LD503.3
C4_D196: LD503.1, LD504.3
C4_D197: LD504.1, LD505.3
C4_D198: LD505.1, LD506.3
C4_D199: LD506.1, LD507.3
C4_D200: LD507.1, LD508.3
C4_D201: LD508.1, LD509.3
C4_D202: LD509.1, LD510.3
C4_D203: LD510.1, LD511.3
C4_D204: LD511.1, LD512.3
C4_D205: LD512.1, LD513.3
C4_D206: LD513.1, LD514.3
C4_D207: LD514.1, LD515.3
C4_D208: LD515.1, LD516.3
C4_D209: LD516.1, LD517.3
C4_D210: LD517.1, LD518.3
C4_D211: LD518.1, LD519.3
C4_D212: LD519.1, LD520.3
C4_D213: LD520.1, LD521.3
C4_D214: LD521.1, LD522.3
C4_K0: JH11.1, LD308.4
C4_K1: LD308.6, LD309.4
C4_K2: LD309.6, LD310.4
C4_K3: LD310.6, LD311.4
C4_K4: LD311.6, LD312.4
C4_K5: LD312.6, LD313.4
C4_K6: LD313.6, LD314.4
C4_K7: LD314.6, LD315.4
C4_K8: LD315.6, LD316.4
C4_K9: LD316.6, LD317.4
C4_K10: LD317.6, LD318.4
C4_K11: LD318.6, LD319.4
C4_K12: LD319.6, LD320.4
C4_K13: LD320.6, LD321.4
C4_K14: LD321.6, LD322.4
C4_K15: LD322.6, LD323.4
C4_K16: LD323.6, LD324.4
C4_K17: LD324.6, LD325.4
C4_K18: LD325.6, LD326.4
C4_K19: LD326.6, LD327.4
C4_K20: LD327.6, LD328.4
C4_K21: LD328.6, LD329.4
C4_K22: LD329.6, LD330.4
C4_K23: LD330.6, LD331.4
C4_K24: LD331.6, LD332.4
C4_K25: LD332.6, LD333.4
C4_K26: LD333.6, LD334.4
C4_K27: LD334.6, LD335.4
C4_K28: LD335.6, LD336.4
C4_K29: LD336.6, LD337.4
C4_K30: LD337.6, LD338.4
C4_K31: LD338.6, LD339.4
C4_K32: LD339.6, LD340.4
C4_K33: LD340.6, LD341.4
C4_K34: LD341.6, LD342.4
C4_K35: LD342.6, LD343.4
C4_K36: LD343.6, LD344.4
C4_K37: LD344.6, LD345.4
C4_K38: LD345.6, LD346.4
C4_K39: LD346.6, LD347.4
C4_K40: LD347.6, LD348.4
C4_K41: LD348.6, LD349.4
C4_K42: LD349.6, LD350.4
C4_K43: LD350.6, LD351.4
C4_K44: LD351.6, LD352.4
C4_K45: LD352.6, LD353.4
C4_K46: LD353.6, LD354.4
C4_K47: LD354.6, LD355.4
C4_K48: LD355.6, LD356.4
C4_K49: LD356.6, LD357.4
C4_K50: LD357.6, LD358.4
C4_K51: LD358.6, LD359.4
C4_K52: LD359.6, LD360.4
C4_K53: LD360.6, LD361.4
C4_K54: LD361.6, LD362.4
C4_K55: LD362.6, LD363.4
C4_K56: LD363.6, LD364.4
C4_K57: LD364.6, LD365.4
C4_K58: LD365.6, LD366.4
C4_K59: LD366.6, LD367.4
C4_K60: LD367.6, LD368.4
C4_K61: LD368.6, LD369.4
C4_K62: LD369.6, LD370.4
C4_K63: LD370.6, LD371.4
C4_K64: LD371.6, LD372.4
C4_K65: LD372.6, LD373.4
C4_K66: LD373.6, LD374.4
C4_K67: LD374.6, LD375.4
C4_K68: LD375.6, LD376.4
C4_K69: LD376.6, LD377.4
C4_K70: LD377.6, LD378.4
C4_K71: LD378.6, LD379.4
C4_K72: LD379.6, LD380.4
C4_K73: LD380.6, LD381.4
C4_K74: LD381.6, LD382.4
C4_K75: LD382.6, LD383.4
C4_K76: LD383.6, LD384.4
C4_K77: LD384.6, LD385.4
C4_K78: LD385.6, LD386.4
C4_K79: LD386.6, LD387.4
C4_K80: LD387.6, LD388.4
C4_K81: LD388.6, LD389.4
C4_K82: LD389.6, LD390.4
C4_K83: LD390.6, LD391.4
C4_K84: LD391.6, LD392.4
C4_K85: LD392.6, LD393.4
C4_K86: LD393.6, LD394.4
C4_K87: LD394.6, LD395.4
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
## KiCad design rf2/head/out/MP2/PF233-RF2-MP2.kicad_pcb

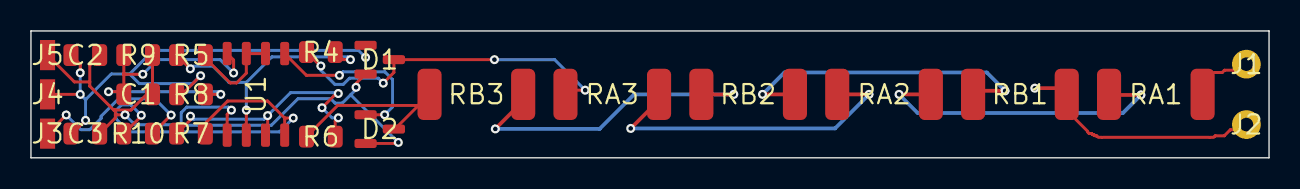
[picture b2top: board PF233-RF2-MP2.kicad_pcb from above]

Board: 2 copper layers, 82.0 x 8.4 mm, 24 parts (0 on the bottom side), 16 nets.

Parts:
C1, C3: 100n; C0805
C2: 10u; C0805
D1, D2: BAV199
J1: PRX_A; WIRE_SENSE
J2: PRX_B; WIRE_SENSE
J3: PRX_OUT; FLEX_PAD
J4: +5VA; FLEX_PAD
J5: AGND; FLEX_PAD
R4, R6: 1k; R0805
R5, R7: 24k; R0805
R8, R9: 10k; R0805
R10: 100R; R0805
RA1, RA2, RA3: 470R CRCW2512; R2512
RB1, RB2, RB3: 470R CRCW2512; R2512
U1: OPA2211AIDR; OPA2211

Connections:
+5VA: C2.1, C3.1, D1.2, D2.2, J4.1, R8.1, U1.8
AGND: C1.2, C2.2, C3.2, D1.1, D2.1, J5.1, R9.2, U1.4
HA1: RA1.2, RA2.1
HA2: RA2.2, RA3.1
HB1: RB1.2, RB2.1
HB2: RB2.2, RB3.1
INN: D2.3, R6.1, RB3.2
INP: D1.3, R4.1, RA3.2
MINUS_A: R6.2, R7.1, U1.2
OUT_A: R7.2, R10.1, U1.1
PLUS_A: R4.2, R5.1, U1.3
PRX_A: J1.1, RA1.1
PRX_B: J2.1, RB1.1
PRX_OUT: J3.1, R10.2
VBIAS: R5.2, U1.6, U1.7
VDIV: C1.1, R8.2, R9.1, U1.5

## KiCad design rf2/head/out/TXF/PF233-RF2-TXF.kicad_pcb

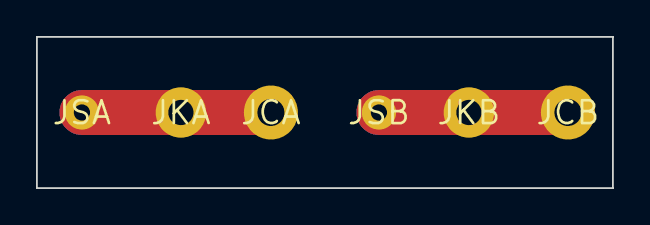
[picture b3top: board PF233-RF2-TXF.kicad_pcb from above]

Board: 2 copper layers, 32.0 x 8.4 mm, 6 parts (0 on the bottom side), 2 nets.

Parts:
JCA: coil A; WIRE_LITZ
JCB: coil B; WIRE_LITZ
JKA: cable A; WIRE_AWG18
JKB: cable B; WIRE_AWG18
JSA: sense A; WIRE_SENSE
JSB: sense B; WIRE_SENSE

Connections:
TX_A: JCA.1, JKA.1, JSA.1
TX_B: JCB.1, JKB.1, JSB.1
